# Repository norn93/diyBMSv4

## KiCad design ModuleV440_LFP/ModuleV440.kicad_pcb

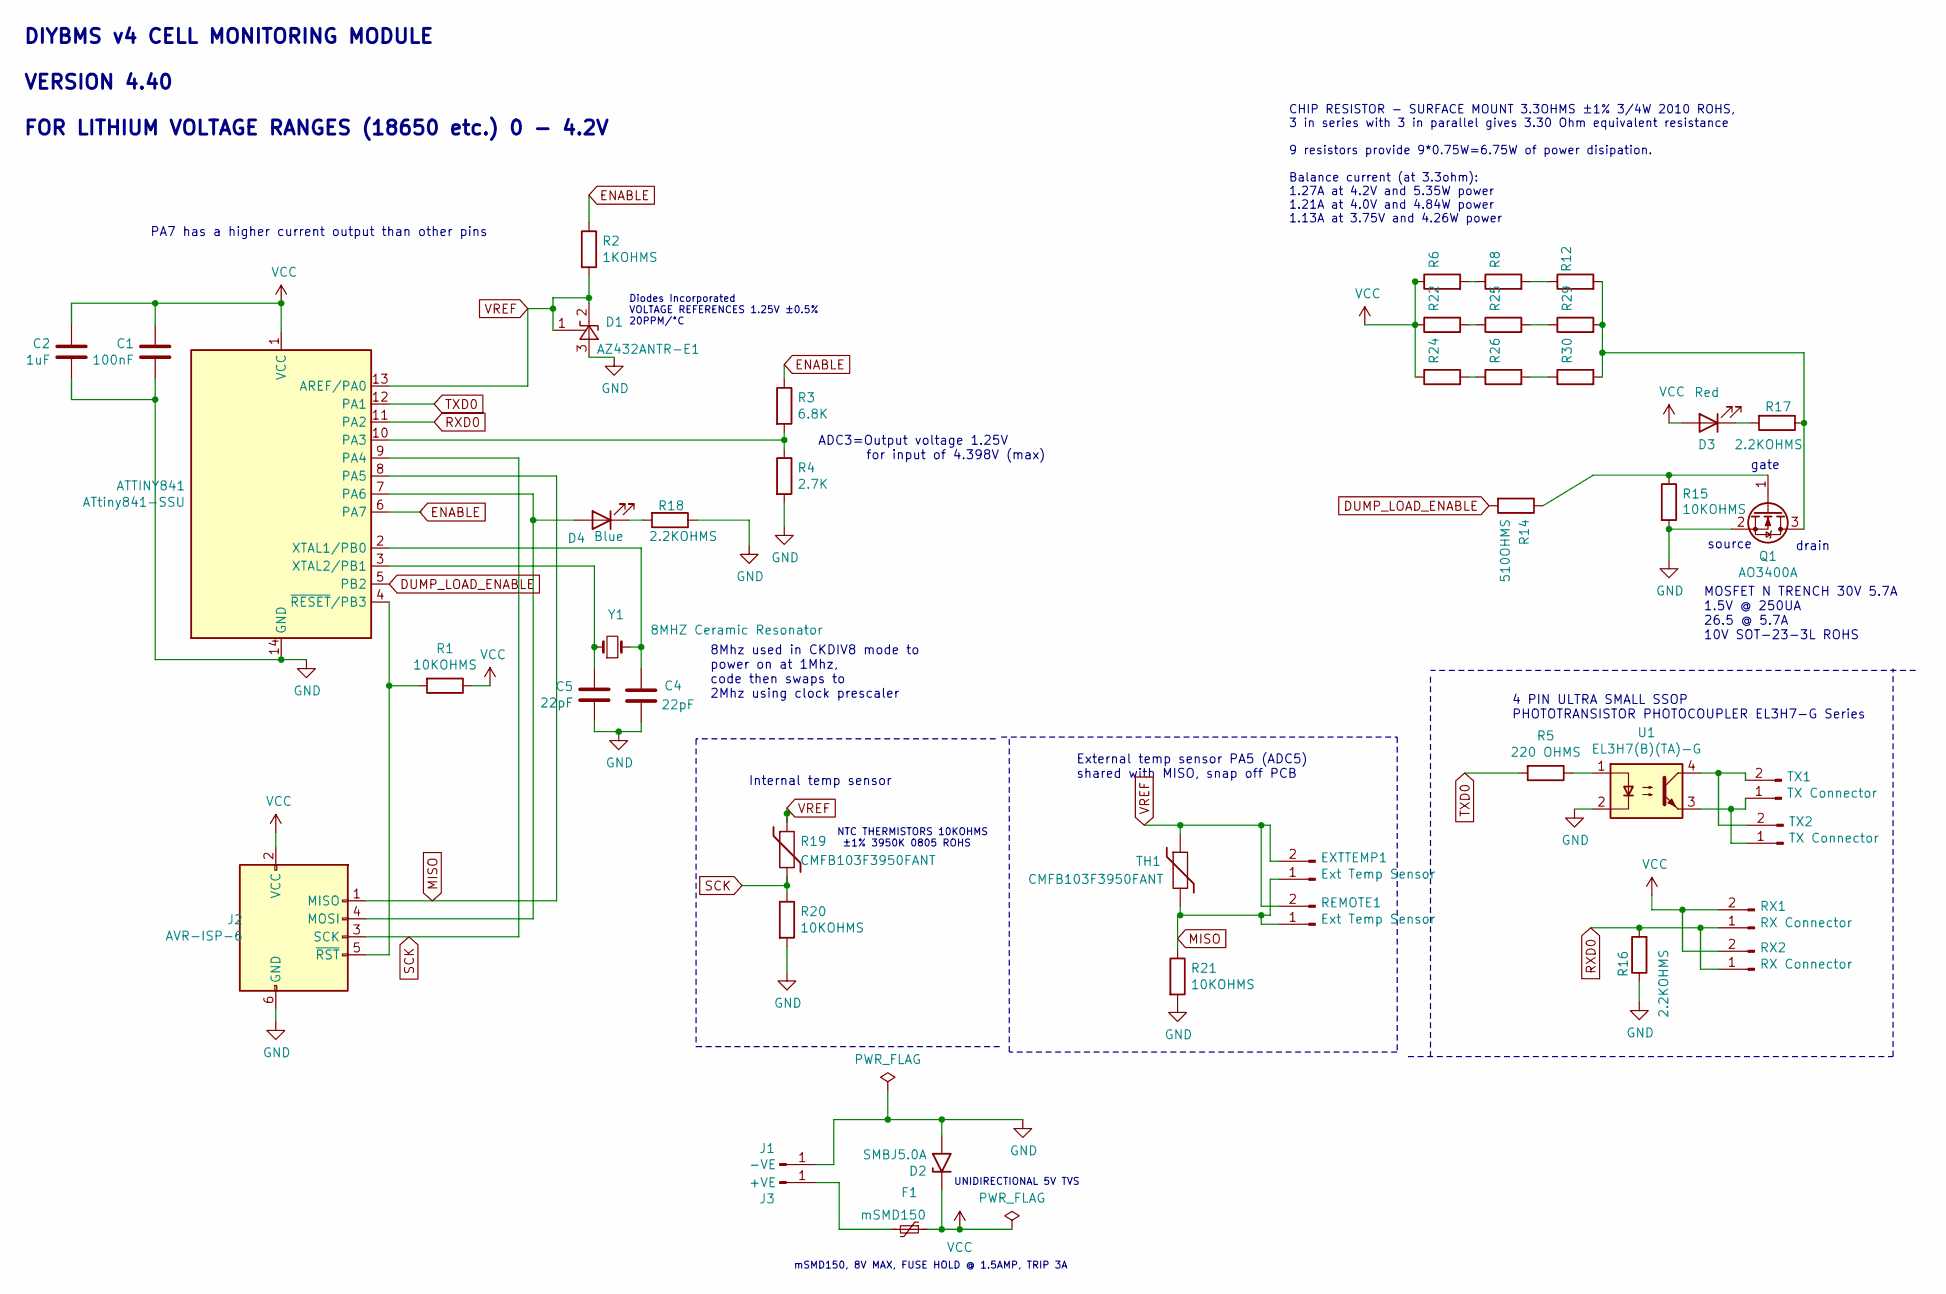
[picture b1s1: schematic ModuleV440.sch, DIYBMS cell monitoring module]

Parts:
ATTINY841: ATtiny841-SSU; SOIC-14_3.9x8.7mm_P1.27mm; LCSCStockCode C219103
C1: 100nF; C_0805_2012Metric; PartNumber CC0805KRX7R9BB104; LCSCStockCode C49678
C2: 1uF; C_0805_2012Metric; PartNumber CL21B105KBFNNNE; LCSCStockCode C28323
C4, C5: 22pF; C_0805_2012Metric; PartNumber CL21C220JBANNNC; LCSCStockCode C1804
D1: AZ432ANTR-E1; SOT-23; PartNumber AZ432ANTR-E1; LCSCStockCode C84139
D2: SMBJ5.0A; D_SMB; LCSCStockCode C440263
D3: Red; LED_0805_2012Metric; PartNumber 2012HRK-620D; LCSCStockCode C84256
D4: Blue; LED_0805_2012Metric; PartNumber Blue LED; LCSCStockCode C2293
EXTTEMP1: Ext Temp Sensor; JST_PH_S2B-PH-K_1x02_P2.00mm_Horizontal; PartNumber S2B-PH-K(LF)(SN); LCSCStockCode C265016
F1: mSMD150; Fuse_1812_4532Metric; PartNumber mSMD150; LCSCStockCode C70121
J1: -VE; MountingHole_6.4mm_M6_Pad_Via
J2: AVR-ISP-6; Pin_Header_Straight_2x03_Pitch2.54mm; LCSCStockCode C65114
J3: +VE; MountingHole_6.4mm_M6_Pad_Via
Q1: AO3400A; SOT-23; PartNumber AO3400A; LCSCStockCode C20917
R1, R15, R20, R21: 10KOHMS; R_0805_2012Metric; PartNumber 0805W8F1002T5E; LCSCStockCode C17414
R2: 1KOHMS; R_0805_2012Metric; PartNumber 0805W8F1001T5E; LCSCStockCode C17513
R3: 6.8K; R_0805_2012Metric; PartNumber 0805W8F6801T5E; LCSCStockCode C17772
R4: 2.7K; R_0805_2012Metric; PartNumber 0805W8F2701T5E; LCSCStockCode C17530
R5: 220 OHMS; R_0805_2012Metric; PartNumber 0805W8F2200T5E; LCSCStockCode C17557
R6, R8, R12, R22, R24, R25, R26, R29, R30: 3.3OHM 3/4W; R_2010_5025Metric; PartNumber 201007F330KT4E; LCSCStockCode C270971
R14: 510OHMS; R_0805_2012Metric; PartNumber 0805W8F5100T5E; LCSCStockCode C17734
R16, R17, R18: 2.2KOHMS; R_0805_2012Metric; PartNumber 0805W8F2201T5E; LCSCStockCode C17520
R19: CMFB103F3950FANT; R_0805_2012Metric; PartNumber CMFB103F3950FANT; LCSCStockCode C51597
REMOTE1: Ext Temp Sensor; JST_PH_S2B-PH-K_1x02_P2.00mm_Horizontal; PartNumber S2B-PH-K(LF)(SN); LCSCStockCode C265016
RX1, RX2: RX Connector; JST_PH_S2B-PH-K_1x02_P2.00mm_Horizontal; PartNumber S2B-PH-K(LF)(SN); LCSCStockCode C265016
TH1: CMFB103F3950FANT; R_0805_2012Metric; PartNumber CMFB103F3950FANT
TX1, TX2: TX Connector; JST_PH_S2B-PH-K_1x02_P2.00mm_Horizontal; PartNumber S2B-PH-K(LF)(SN); LCSCStockCode C265016
U1: EL3H7(B)(TA)-G; SOP-4_4.4x2.6mm_P1.27mm; PartNumber EL3H7(B)(TA)-G; LCSCStockCode C32565
Y1: 8MHZ Ceramic Resonator; Crystal_SMD_5032-2pin_5.0x3.2mm; PartNumber X50328MSB2GI; LCSCStockCode C115962

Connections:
DUMP_LOAD_ENABLE: ATTINY841.5 (PB2), R14.2
ENABLE: ATTINY841.6 (PA7), R2.1, R3.1
GND: ATTINY841.14 (GND), C1.2, C2.2, C4.2, C5.2, D1.3 (A), D2.2 (A2), J1.1, J2.6 (GND), Q1.2 (S), R4.2, R15.2, R16.1, R18.1, R20.2, R21.2, U1.2
MISO: ATTINY841.8 (PA5), EXTTEMP1.1, J2.1 (MISO), R21.1, REMOTE1.1, TH1.2
unnamed: ATTINY841.2 (XTAL1/PB0), C4.1, Y1.2
unnamed: ATTINY841.3 (XTAL2/PB1), C5.1, Y1.1
unnamed: ATTINY841.4 (~RESET~/PB3), J2.5 (~RST), R1.2
unnamed: ATTINY841.7 (PA6), D4.2 (A), J2.4 (MOSI)
unnamed: ATTINY841.10 (PA3), R3.2, R4.1
unnamed: D3.1 (K), R17.2
unnamed: D4.1 (K), R18.2
unnamed: F1.2, J3.1
unnamed: Q1.1 (G), R14.1, R15.1
unnamed: Q1.3 (D), R12.2, R17.1, R29.2, R30.2
unnamed: R5.1, U1.1
unnamed: R6.2, R8.1
unnamed: R8.2, R12.1
unnamed: R22.2, R25.1
unnamed: R24.2, R26.1
unnamed: R25.2, R29.1
unnamed: R26.2, R30.1
unnamed: TX1.1, TX2.1, U1.3
unnamed: TX1.2, TX2.2, U1.4
RXD0: ATTINY841.11 (PA2), R16.2, RX1.1, RX2.1
SCK: ATTINY841.9 (PA4), J2.3 (SCK), R19.2, R20.1
TXD0: ATTINY841.12 (PA1), R5.2
VCC: ATTINY841.1 (VCC), C1.1, C2.1, D2.1 (A1), D3.2 (A), F1.1, J2.2 (VCC), R1.1, R6.1, R22.1, R24.1, RX1.2, RX2.2
VREF: ATTINY841.13 (AREF/PA0), D1.1 (FB), D1.2 (K), EXTTEMP1.2, R2.2, R19.1, REMOTE1.2, TH1.1

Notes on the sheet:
PA7 has a higher current output than other pins
gate
source
drain
4 PIN ULTRA SMALL SSOP PHOTOTRANSISTOR PHOTOCOUPLER EL3H7-G Series
MOSFET N TRENCH 30V 5.7A 1.5V @ 250UA 26.5 @ 5.7A 10V SOT-23-3L ROHS
Diodes Incorporated VOLTAGE REFERENCES 1.25V ±0.5% 20PPM/°C
mSMD150, 8V MAX, FUSE HOLD @ 1.5AMP, TRIP 3A
External temp sensor PA5 (ADC5) shared with MISO, snap off PCB
NTC THERMISTORS 10KOHMS ±1% 3950K 0805 ROHS
ADC3=Output voltage 1.25V for input of 4.398V (max)
8Mhz used in CKDIV8 mode to power on at 1Mhz, code then swaps to 2Mhz using clock prescaler
DIYBMS v4 CELL MONITORING MODULE VERSION 4.40 FOR LITHIUM VOLTAGE RANGES (18650 etc.) 0 - 4.2V
Internal temp sensor
UNIDIRECTIONAL 5V TVS
CHIP RESISTOR - SURFACE MOUNT 3.3OHMS ±1% 3/4W 2010 ROHS, 3 in series with 3 in parallel gives 3.30 Ohm equivalent resistance 9 resistors provide 9*0.75W=6.75W of power disipation. Balance current (at 3.3ohm): 1.27A at 4.2V and 5.35W power 1.21A at 4.0V and 4.84W power 1.13A at 3.75V and 4.26W power

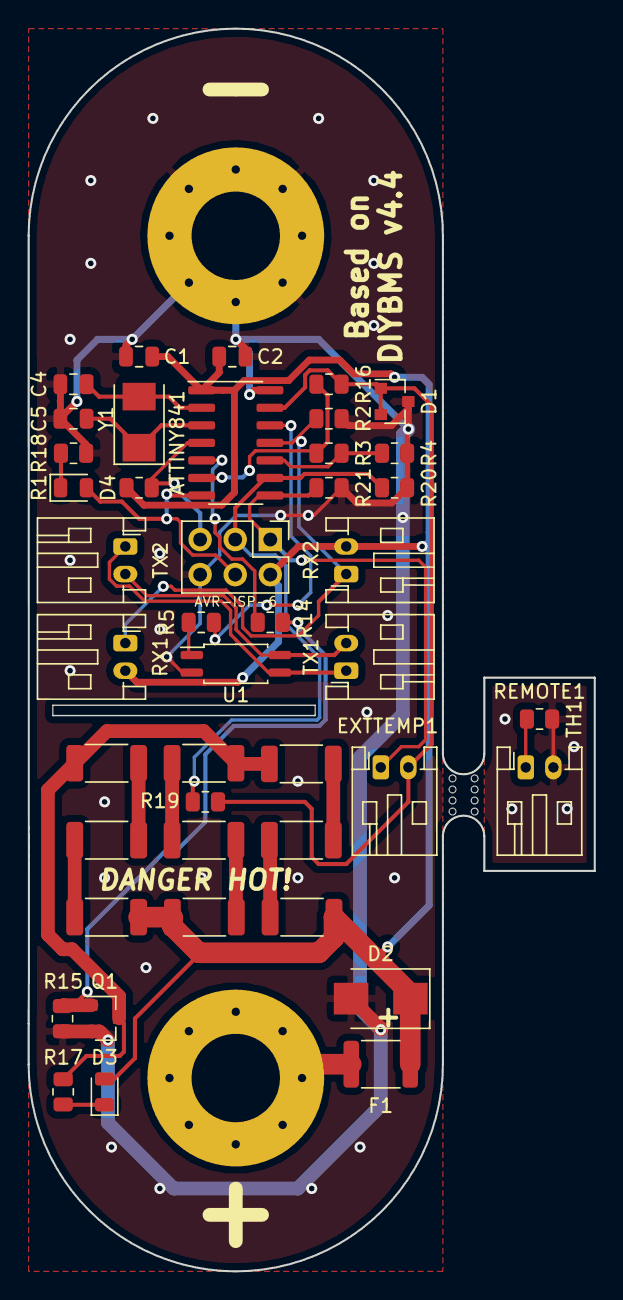
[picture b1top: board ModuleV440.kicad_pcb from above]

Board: 2 copper layers, 41.0 x 90.0 mm, 46 parts (0 on the bottom side), 28 nets.

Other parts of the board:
mouse-bite-3mm-slot: VAL**; mouse-bite-3mm-slot

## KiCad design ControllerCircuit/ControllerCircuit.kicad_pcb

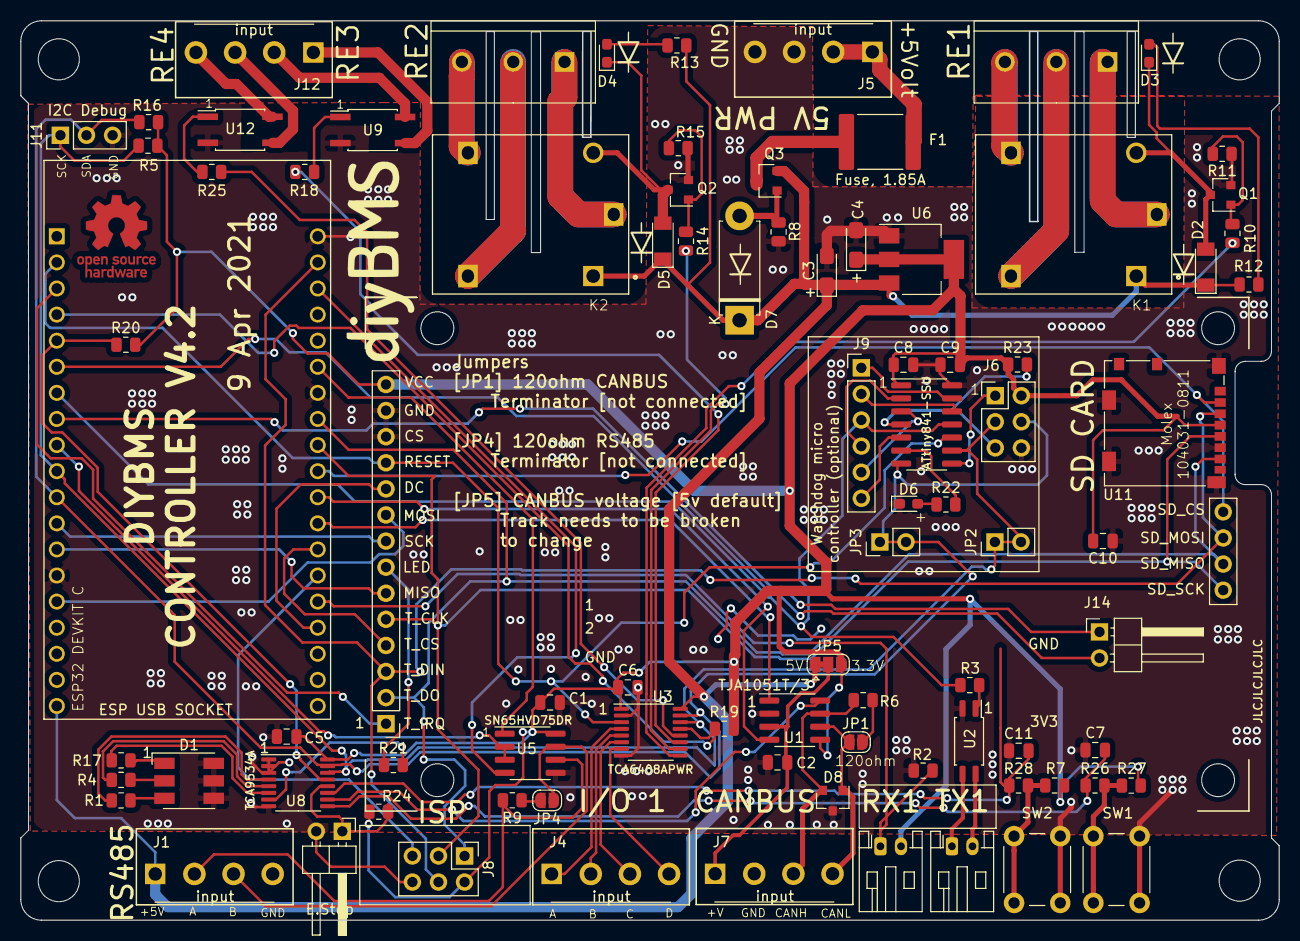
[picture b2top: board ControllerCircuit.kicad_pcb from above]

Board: 2 copper layers, 122.4 x 87.5 mm, 87 parts (0 on the bottom side), 90 nets.

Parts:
C1, C2, C5, C6, C8: 100nF; C_0805_2012Metric
C3, C4: 22uF 6.3V; CP_EIA-3216-18_Kemet-A_Pad1.58x1.35mm_HandSolder
C7, C9, C10, C11: 1uF; C_0805_2012Metric
D1: RGB; LED_RGB_5050-6
D2, D5: LL4148; D_MiniMELF
D3, D4, D6: YELLOW LED; LED_0603_1608Metric_Pad1.05x0.95mm_HandSolder
D7: D_Zener_Small; D_5W_P10.16mm_Horizontal
D8: NUP2105LT1G; SOT-23
F1: Fuse, 1.85A; Fuse_2920_7451Metric
J1, J4, J5, J7, J12: ScrewTerminal; Terminal-Block_3.81_4P_LCSC_C395880
J2, J3: ScrewTerminal3Pin; Terminal-Block_5.0mm_3P-LCSC_C395850
J6: AVR-ISP-6; PinHeader_2x03_P2.54mm_Vertical
J8: 2x3 2.54mm IDC Connectors; PinHeader_2x03_P2.54mm_Vertical
J9: Conn_01x06_Female; PinHeader_1x06_P2.54mm_Vertical
J10: Conn_01x02_Female; PinHeader_1x02_P2.54mm_Horizontal
J11: Conn_01x03_Female; PinHeader_1x03_P2.54mm_Vertical
J14: Receive; PinHeader_1x02_P2.54mm_Horizontal
JP1, JP4: OptTermination; SolderJumper-2_P1.3mm_Open_RoundedPad1.0x1.5mm
JP2, JP3: Conn_01x02_Female; PinHeader_1x02_P2.54mm_Vertical
JP5: CANBUS Volt Select; SolderJumper-3_P1.3mm_Bridged12_RoundedPad1.0x1.5mm
K1, K2: SRD-05VDC-SL-C; RELAY_SRD-05VDC-SL-C
LCD1: LCD; TFTSPI_2_8_240x320_TOUCH
Q1, Q2: AO3400A; SOT-23
Q3: AO3401A; SOT-23
R1, R8: 100R; R_0805_2012Metric
R2, R5, R16: 2K2; R_0805_2012Metric
R3, R21, R22: 180R; R_0805_2012Metric
R4, R17: 300R; R_0805_2012Metric
R6, R9: 120R; R_0805_2012Metric
R7, R27: 51K; R_0805_2012Metric
R10, R14, R18, R25: 220R; R_0805_2012Metric
R11, R15, R19, R20, R23, R24: 10K; R_0805_2012Metric
R12, R13: 560R; R_0805_2012Metric
R26, R28: 22K; R_0805_2012Metric
RX1: Receive; JST_PH_S2B-PH-K_1x02_P2.00mm_Horizontal
SW1, SW2: PTS645SL50-2LFS; SW_PUSH_6mm_H4.3mm
TX1: Transmit; JST_PH_S2B-PH-K_1x02_P2.00mm_Horizontal
U1: TJA1051T/3; SOIC-8_3.9x4.9mm_P1.27mm
U2: EL3H7(B)(TA)-G; SOP-4_4.4x2.6mm_P1.27mm
U3: TCA6408APWR; TSSOP-16_4.4x5mm_P0.65mm
U4: ESP32-DEVKITC-32D; MODULE_ESP32-DEVKITC-32D
U5: SN65HVD75DR; SOIC-8_3.9x4.9mm_P1.27mm
U6: AMS1117-3.3; SOT-223-3_TabPin2
U8: TCA9534A; TSSOP-16_4.4x5mm_P0.65mm
U9, U12: AQY212GSZ; SO-4_4.4x3.6mm_P2.54mm
U10: ATtiny841-SSU; SOIC-14_3.9x8.7mm_P1.27mm
U11: MicroSD_SPI_CD; microSD_HC_Molex_104031-0811

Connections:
+3V3: C1.1, C4.1, C5.2, C6.1, C8.1, C9.2, C10.2, J6.2, J8.2, JP5.3, LCD1.14, R5.2, R7.1, R16.2, R19.2, R20.2, R23.1, R24.2, R27.1, RX1.2, U1.5, U3.1, U5.8, U6.2, U8.16, U10.1, U11.4
+5V: F1.2, J5.1, J5.2
/AVRISP_RESET: J8.5, U4.33
/BLUE_LED: R1.2, U8.4
/CANBUS_RX: U1.4, U4.30
/CANBUS_S: U1.8, U8.10
/CANBUS_TX: U1.1, U4.31
/DISPLAY_DC: LCD1.10, U4.35
/DISPLAY_LED: R21.2, U8.7
/EXT_IO_A: J4.1, U3.4
/EXT_IO_B: J4.2, U3.5
/EXT_IO_C: J4.3, U3.6
/EXT_IO_D: J4.4, U3.7
/GREEN_LED: R17.2, U8.6
/HSPI_CLK: LCD1.8, U4.12
/HSPI_MISO: LCD1.6, U4.13
/HSPI_MOSI: LCD1.9, U4.15
/IO2: R2.2, RX1.1, U4.34
/IO4: LCD1.4, U4.32
/IO5: LCD1.SD4, U4.29, U11.2
/IO21: U4.25, U5.1
/IO22: U4.22, U5.4
/IO25: U4.9, U5.2, U5.3
/IO26: J6.3, J11.1, JP2.1, JP2.2, R5.1, U3.14, U4.10, U8.14, U10.9
/IO27: J6.4, J11.2, JP3.1, JP3.2, R16.1, U3.15, U4.11, U8.15, U10.7
/IO32: J9.3, R3.2, U4.7, U10.11
/IO33: J14.1, U4.8
/IO34_INPUT: R20.1, U4.5, U8.13
/IO35_INPUT: J14.2, U4.6
/IO36_INPUT: LCD1.1, U4.3
/IO39_INPUT: R19.1, U3.13, U4.4
/RED_LED: R4.2, U8.5
/RELAY1: R10.2, U3.9
/RELAY2: R14.2, U3.10
/RELAY3_SSR: R18.2, U3.11
/RELAY4_SSR: R25.2, U3.12
/RESET: LCD1.11, U3.3, U4.2, U10.10
/SW1OUTPUT: C7.2, R26.1, U8.9
/SW2OUTPUT: C11.2, R28.1, U8.11
/VSPI_CLK: J8.3, LCD1.5, LCD1.SD1, U4.28, U11.5
/VSPI_MISO: J8.1, LCD1.2, LCD1.SD2, U4.27, U11.7
/VSPI_MOSI: J8.4, LCD1.3, LCD1.SD3, U4.21, U11.3
FUSED5V: C3.1, D2.1, D5.1, D7.1, J1.1, JP5.1, K1.A1, K2.A1, Q3.2, R12.2, R13.2, U3.16, U4.19, U6.3
GND: C1.2, C2.2, C3.2, C4.2, C5.1, C6.2, C7.1, C8.2, C9.1, C10.1, C11.1, D1.4, D1.5, D1.6, D6.1, D8.3, J1.4, J5.3, J5.4, J6.6, J7.2, J8.6, J10.2, J11.3, LCD1.12, LCD1.13, Q1.2, Q2.2, R2.1, R8.2, R11.1, R15.1, SW1.2, SW2.2, U1.2, U2.2, U3.2, U3.8, U4.14, U4.20, U4.26, U5.5, U6.1, U8.1, U8.2, U8.3, U8.8, U9.2, U10.14, U11.6, U11.11, U12.2
unnamed: C2.1, J7.1, JP5.2, U1.3
unnamed: D1.1, R17.1
unnamed: D1.2, R4.1
unnamed: D1.3, R1.1
unnamed: D2.2, D3.1, K1.A2, Q1.3
unnamed: D3.2, R12.1
unnamed: D4.1, D5.2, K2.A2, Q2.3
unnamed: D4.2, R13.1
unnamed: D6.2, R22.1
unnamed: D7.2, Q3.1, R8.1
unnamed: D8.1, J7.4, JP1.1, U1.6
unnamed: D8.2, J7.3, R6.2, U1.7
unnamed: F1.1, Q3.3
unnamed: J1.2, R9.1, U5.6
unnamed: J1.3, JP4.1, U5.7
unnamed: J2.1, K1.COM
unnamed: J2.2, K1.NC
unnamed: J2.3, K1.NO
unnamed: J3.1, K2.COM
unnamed: J3.2, K2.NC
unnamed: J3.3, K2.NO
unnamed: J6.1, U10.8
unnamed: J6.5, R23.2, U10.4
unnamed: J9.1, U10.13
unnamed: J9.2, U10.12
unnamed: J9.4, U10.2
unnamed: J9.5, U10.3
unnamed: J9.6, U10.5
unnamed: J10.1, R24.1, U8.12
unnamed: J12.1, U9.3
unnamed: J12.2, U9.4
unnamed: J12.3, U12.3
unnamed: J12.4, U12.4
unnamed: JP1.2, R6.1
unnamed: JP4.2, R9.2
unnamed: LCD1.7, R21.1
unnamed: Q1.1, R10.1, R11.2
unnamed: Q2.1, R14.1, R15.2
unnamed: R3.1, U2.1
unnamed: R18.1, U9.1
unnamed: R22.2, U10.6
unnamed: R25.1, U12.1
unnamed: R26.2, R27.2, SW1.1
unnamed: R7.2, R28.2, SW2.1
unnamed: TX1.1, U2.3
unnamed: TX1.2, U2.4

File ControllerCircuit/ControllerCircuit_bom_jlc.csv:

"Comment","Designator","Footprint","LCSC Part #"
"100nF","C1,C2,C6,C8,C5","C_0805_2012Metric","C49678"
"22uF 6.3V","C3,C4","CP_EIA-3216-18_Kemet-A_Pad1.58x1.35mm_HandSolder","C126948"
"1uF","C9,C10","C_0805_2012Metric","C28323"
"RGB","D1","LED_RGB_5050-6","C219409"
"LL4148","D2,D5","D_MiniMELF","C9808"
"YELLOW LED","D3,D4,D6","LED_0603_1608Metric_Pad1.05x0.95mm_HandSolder","C72038"
"NUP2105LT1G","D8","SOT-23","C14486"
"Fuse, 1.85A","F1","Fuse_2920_7451Metric","C262041"
"ScrewTerminal","J1,J4,J7,J12,J5","Terminal-Block_3.81_4P_LCSC_C395880","C395880"
"ScrewTerminal3Pin","J3,J2","Terminal-Block_5.0mm_3P-LCSC_C395850","C395850"
"AVR-ISP-6","J6","PinHeader_2x03_P2.54mm_Vertical","C65114"
"2x3 2.54mm IDC Connectors","J8","PinHeader_2x03_P2.54mm_Vertical","C132438"
"Conn_01x02_Female","J10","PinHeader_1x02_P2.54mm_Horizontal","C376120"
"SRD-05VDC-SL-C","K1,K2","RELAY_SRD-05VDC-SL-C","C35449"
"AO3400A","Q1,Q2","SOT-23","C344010"
"AO3401A","Q3","SOT-23","C15127"
"180R","R3,R21,R22","R_0805_2012Metric","C25270"
"300R","R4,R17","R_0805_2012Metric","C17617"
"2K2","R5,R16,R2","R_0805_2012Metric","C17520"
"120R","R6,R9","R_0805_2012Metric","C17437"
"100R","R8,R1","R_0805_2012Metric","C17408"
"220R","R10,R14,R18,R25","R_0805_2012Metric","C17557"
"10K","R11,R15,R19,R20,R23,R24,R27,R7","R_0805_2012Metric","C17414"
"560R","R12,R13","R_0805_2012Metric","C28636"
"Receive","RX1","JST_PH_S2B-PH-K_1x02_P2.00mm_Horizontal","C157932"
"PTS645SL50-2LFS","SW1,SW2","SW_PUSH_6mm_H4.3mm","C221876"
"Transmit","TX1","JST_PH_S2B-PH-K_1x02_P2.00mm_Horizontal","C157932"
"TJA1051T/3","U1","SOIC-8_3.9x4.9mm_P1.27mm","C38695"
"EL3H7(B)(TA)-G","U2","SOP-4_4.4x2.6mm_P1.27mm","C32565"
"TCA6408APWR","U3","TSSOP-16_4.4x5mm_P0.65mm","C206177"
"SN65HVD75DR","U5","SOIC-8_3.9x4.9mm_P1.27mm","C57928"
"AMS1117-3.3","U6","SOT-223-3_TabPin2","C6186"
"TCA9534A","U8","TSSOP-16_4.4x5mm_P0.65mm","C206010"
"AQY212GSZ","U9,U12","SO-4_4.4x3.6mm_P2.54mm","C129283"
"MicroSD_SPI_CD","U11","microSD_HC_Molex_104031-0811","C585350"

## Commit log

2021-03-10 Add pull up to J13 for remote touch display
2021-03-11 Tidy up track
2021-03-11 Controller gerbers
2021-03-11 Updated BOM
2021-03-11 Programming adapter board
2021-04-05 Added push button switch to wake TFT
2021-04-05 Reduced solder footprint for fuse
2021-04-05 Move LEDs near relays (improve seperation)
2021-04-06 Updated Patreon list on silkscreen
2021-04-06 Add OPENSCAD to GITHUB action
2021-04-08 Issue #78 swap of TCA6408APWR
2021-04-08 Added SW1 and SW2 to replace J13
2021-04-13 Added SW1 and SW2
2022-01-16 Added 60 Ah LFP module

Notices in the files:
ControllerCircuit/ControllerCircuit.kicad_pcb:
©2019 to 2021 Stuart Pittaway
